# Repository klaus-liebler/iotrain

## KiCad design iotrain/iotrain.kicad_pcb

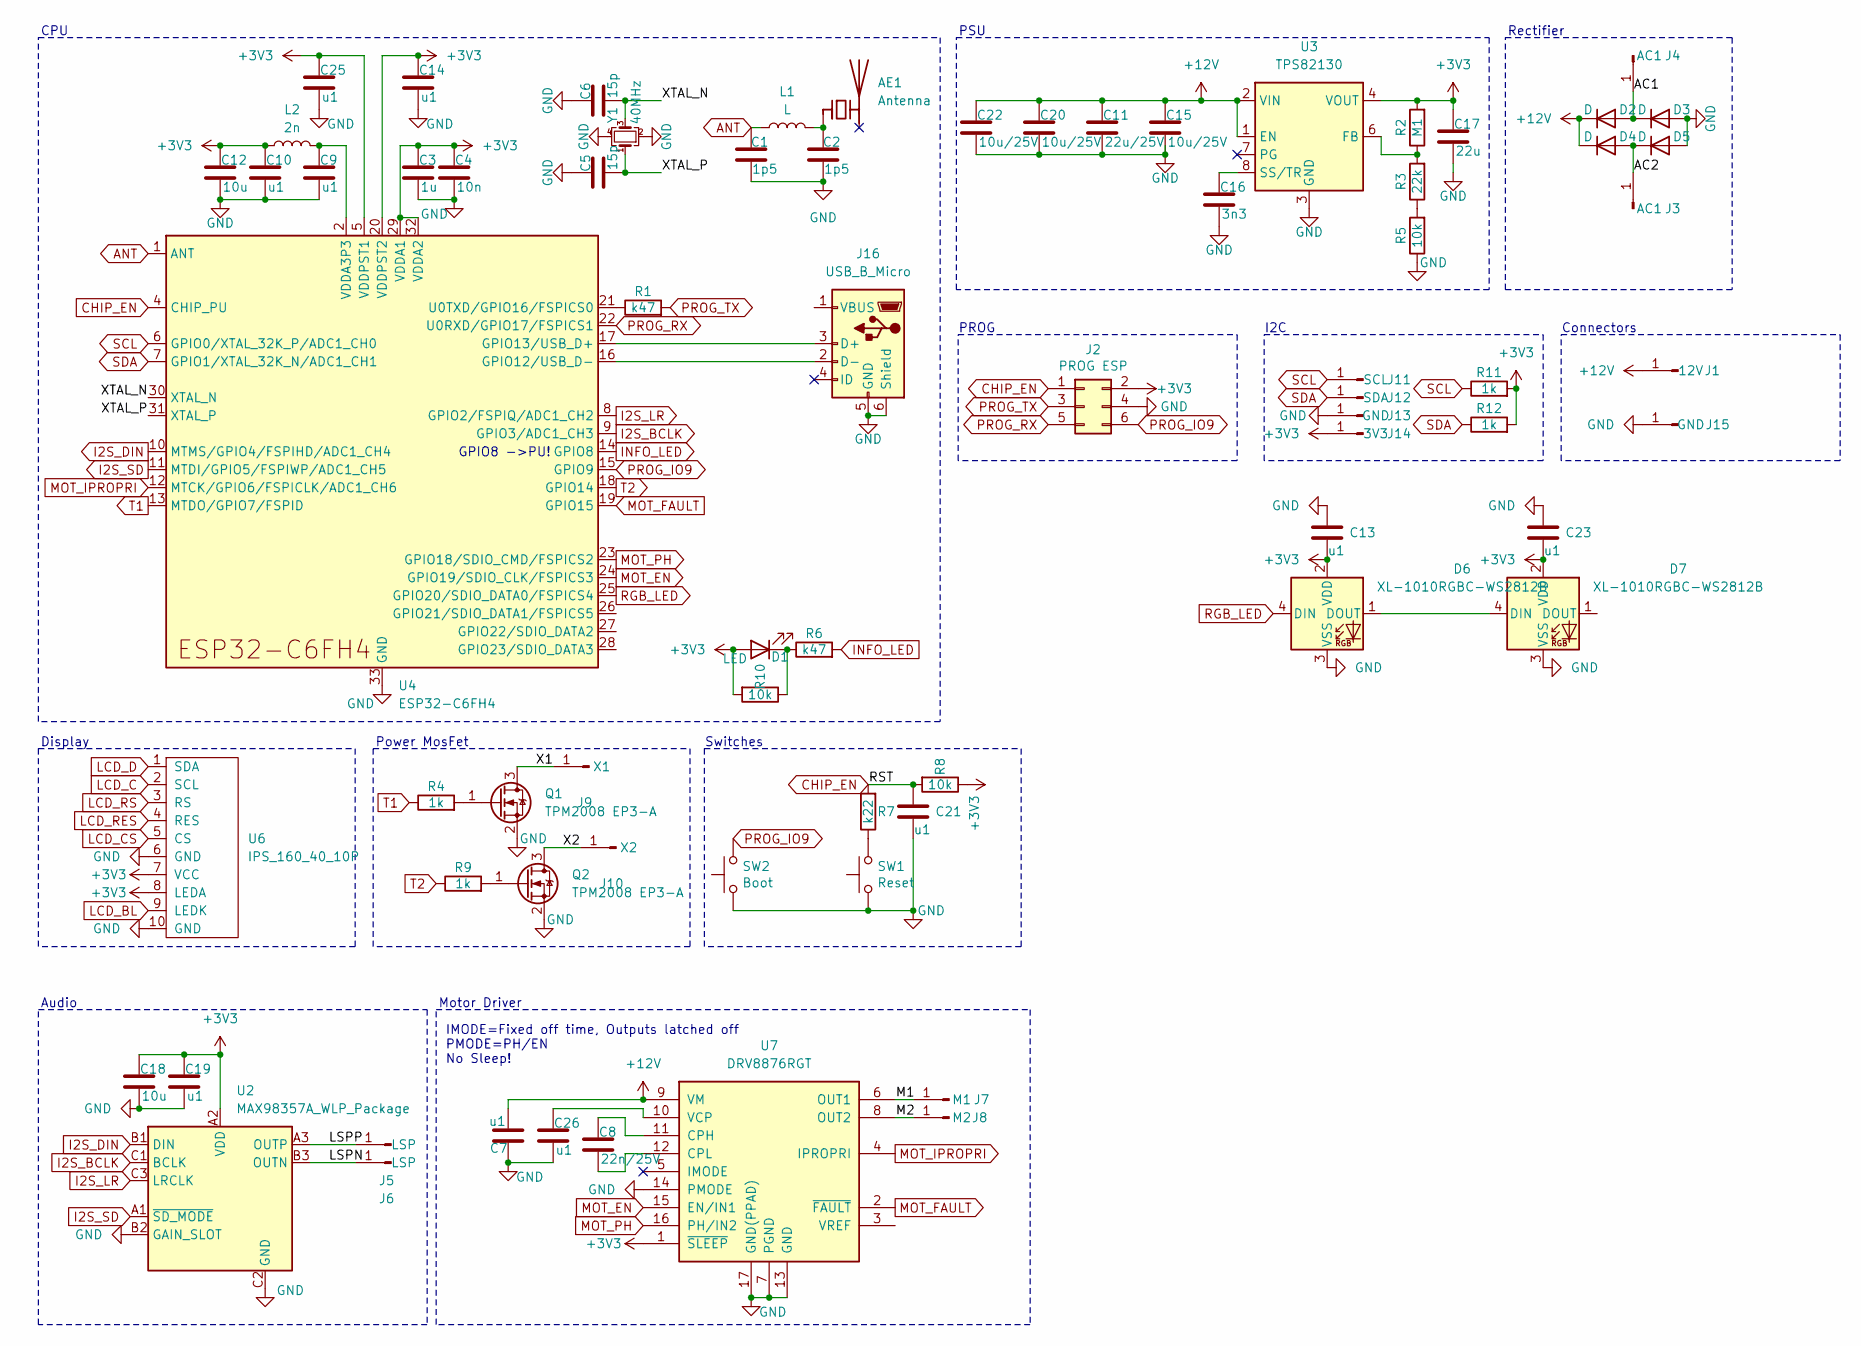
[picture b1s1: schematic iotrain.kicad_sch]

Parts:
AE1: Antenna; Johanson_2450AT18x100
C1, C2: 1p5; SMD0201
C3: 1u; SMD0201
C4: 10n; SMD0201
C5, C6: 15p; SMD0201
C7, C9, C10, C13, C14, C19, C21, C23, C25, C26: u1; SMD0201
C8: 22n/25V; SMD0201
C11: 22u/25V; SMD0805
C12, C18: 10u; SMD0402
C15, C20, C22: 10u/25V; SMD0603
C16: 3n3; SMD0201
C17: 22u; SMD0402
D1: LED; LED_0402_1005Metric
D2, D3, D4, D5: D; D_SOD-123F_smaller
D6, D7: XL-1010RGBC-WS2812B
J1: 12V; SolderWirePad_1x01_SMD_1x2mm
J2: PROG ESP; Tag-Connect_TC2030-IDC-NL_2x03_P1.27mm_Vertical
J3, J4: AC1; SolderWirePad_1x01_SMD_1x2mm
J5, J6: LSP; SolderWirePad_1x01_SMD_1x2mm
J7: M1; SolderWirePad_1x01_SMD_1x2mm
J8: M2; SolderWirePad_1x01_SMD_1x2mm
J9: X1; SolderWirePad_1x01_SMD_1x2mm
J10: X2; SolderWirePad_1x01_SMD_1x2mm
J11: SCL; SolderWirePad_1x01_SMD_1x2mm
J12: SDA; SolderWirePad_1x01_SMD_1x2mm
J13, J15: GND; SolderWirePad_1x01_SMD_1x2mm
J14: 3V3; SolderWirePad_1x01_SMD_1x2mm
J16: USB_B_Micro; USB_Micro-B_Amphenol_10104110_Horizontal
L1: L; SMD0201
L2: 2n; SMD0201
Q1, Q2: TPM2008 EP3-A; Diodes_DFN1006-3
R1, R6: k47; SMD0201
R2: M1; SMD0201
R3: 22k; SMD0201
R4, R9, R11, R12: 1k; SMD0201
R5, R8, R10: 10k; SMD0201
R7: k22; SMD0201
SW1: Reset; SW_Push_SPST_NO_Alps_SKRK
SW2: Boot; SW_Push_SPST_NO_Alps_SKRK
U2: MAX98357A_WLP_Package; WLP-9_1.448x1.468mm_Layout3x3_P0.4mm_Ball0.27mm_Pad0.25mm
U3: TPS82130; Texas_SIL0008D_MicroSiP-8-1EP_2.8x3mm_P0.65mm_EP1.1x1.9mm_T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
U4: ESP32-C6FH4; QFN-32-1EP_5x5mm_P0.5mm_EP3.6x3.6mm
U6: IPS_160_40_10P; IPS LCD 0.99 40x160
U7: DRV8876RGT; UQFN-16-1EP_3x3mm_P0.5mm_EP1.75x1.75mm
Y1: 40MHz; Crystal_SMD_2016-4Pin_2.0x1.6mm

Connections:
+3V3: C3.1, C4.1, C10.1, C12.1, C13.2, C14.1, C17.1, C18.1, C19.1, C23.2, C25.1, D1.2 (A), D6.2 (VDD), D7.2 (VDD), J2.2, J14.1, L2.1, R2.2, R8.1, R10.2, R11.2, R12.2, U2.A2 (VDD), U3.4 (VOUT), U3.5 (VOUT), U4.5 (VDDPST1), U4.20 (VDDPST2), U4.29 (VDDA1), U4.32 (VDDA2), U6.7 (VCC), U6.8 (LEDA), U7.1 (~SLEEP); also elsewhere on the board
+12V: C7.2, C11.1, C15.1, C20.1, C22.1, D2.1 (K), D4.1 (K), J1.1, U3.1 (EN), U3.2 (VIN), U7.9 (VM)
/AC1: D2.2 (A), D3.1 (K), J4.1
/AC2: D4.2 (A), D5.1 (K), J3.1
/LSPN: J6.1, U2.B3 (OUTN)
/LSPP: J5.1, U2.A3 (OUTP)
/M1: J7.1, U7.6 (OUT1)
/M2: J8.1, U7.8 (OUT2)
/X1: J9.1, Q1.3 (D)
/X2: J10.1, Q2.3 (D)
/XTAL_N: C6.2, U4.30 (XTAL_N), Y1.3
/XTAL_P: C5.2, U4.31 (XTAL_P), Y1.1
ANT: C1.1, L1.2, U4.1 (ANT)
CHIP_EN: C21.1, J2.1, R7.2, R8.2, U4.4 (CHIP_PU)
GND: C1.2, C2.2, C3.2, C4.2, C5.1, C6.1, C7.1, C9.2, C10.2, C11.2, C12.2, C13.1, C14.2, C15.2, C16.2, C17.2, C18.2, C19.2, C20.2, C21.2, C22.2, C23.1, C25.2, C26.2, D3.2 (A), D5.2 (A), D6.3 (VSS), D7.3 (VSS), J2.4, J13.1, J15.1, J16.5 (GND), J16.6 (Shield), Q1.2 (S), Q2.2 (S), R5.1, SW1.1, SW2.1, U2.B2 (GAIN_SLOT), U2.C2 (GND), U3.3 (GND), U3.9 (GND), U4.33 (GND), U6.6 (GND), U6.10 (GND), U7.7 (PGND), U7.13 (GND), U7.14 (PMODE), U7.17 (GND(PPAD)), Y1.2, Y1.4; also elsewhere on the board
I2S_BCLK: U2.C1 (BCLK), U4.9 (GPIO3/ADC1_CH3)
I2S_DIN: U2.B1 (DIN), U4.10 (MTMS/GPIO4/FSPIHD/ADC1_CH4)
I2S_LR: U2.C3 (LRCLK), U4.8 (GPIO2/FSPIQ/ADC1_CH2)
I2S_SD: U2.A1 (~SD_MODE), U4.11 (MTDI/GPIO5/FSPIWP/ADC1_CH5)
INFO_LED: R6.2, U4.14 (GPIO8)
LCD_BL: U6.9 (LEDK)
LCD_C: U6.2 (SCL)
LCD_CS: U6.5 (CS)
LCD_D: U6.1 (SDA)
LCD_RES: U6.4 (RES)
LCD_RS: U6.3 (RS)
MOT_EN: U4.24 (GPIO19/SDIO_CLK/FSPICS3), U7.15 (EN/IN1)
MOT_FAULT: U4.19 (GPIO15), U7.2 (~FAULT)
MOT_IPROPRI: U4.12 (MTCK/GPIO6/FSPICLK/ADC1_CH6), U7.4 (IPROPRI)
MOT_PH: U4.23 (GPIO18/SDIO_CMD/FSPICS2), U7.16 (PH/IN2)
unnamed: AE1.1 (FEED), C2.1, L1.1
unnamed: C9.1, L2.2, U4.2 (VDDA3P3), U4.3 (VDDA3P3)
unnamed: D1.1 (K), R6.1, R10.1
unnamed: D6.1 (DOUT), D7.4 (DIN)
unnamed: J16.3 (D+), U4.17 (GPIO13/USB_D+)
unnamed: J16.2 (D-), U4.16 (GPIO12/USB_D-)
unnamed: Q1.1 (G), R4.2
unnamed: Q2.1 (G), R9.2
unnamed: R3.1, R5.2
unnamed: R7.1, SW1.2
unnamed: R2.1, R3.2, U3.6 (FB)
unnamed: C16.1, U3.8 (SS/TR)
unnamed: R1.1, U4.21 (U0TXD/GPIO16/FSPICS0)
unnamed: C8.1, U7.11 (CPH)
unnamed: C8.2, U7.12 (CPL)
unnamed: C26.1, U7.10 (VCP)
PROG_IO9: J2.6, SW2.2, U4.15 (GPIO9)
PROG_RX: J2.5, U4.22 (U0RXD/GPIO17/FSPICS1)
PROG_TX: J2.3, R1.2
RGB_LED: D6.4 (DIN), U4.25 (GPIO20/SDIO_DATA0/FSPICS4)
SCL: J11.1, R11.1, U4.6 (GPIO0/XTAL_32K_P/ADC1_CH0)
SDA: J12.1, R12.1, U4.7 (GPIO1/XTAL_32K_N/ADC1_CH1)
T1: R4.1, U4.13 (MTDO/GPIO7/FSPID)
T2: R9.1, U4.18 (GPIO14)

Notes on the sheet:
IMODE=Fixed off time, Outputs latched off PMODE=PH/EN No Sleep!
I2C
Rectifier
Connectors
PSU
CPU
Switches
Display
Audio
GPIO8 ->PU!
Power MosFet
Motor Driver
PROG

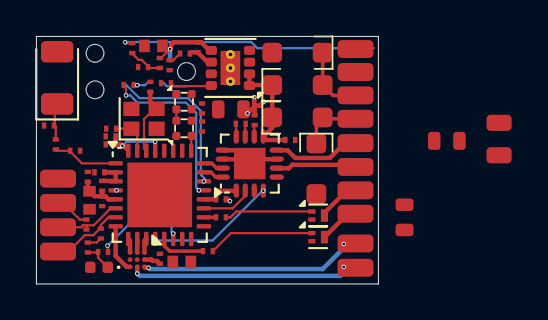
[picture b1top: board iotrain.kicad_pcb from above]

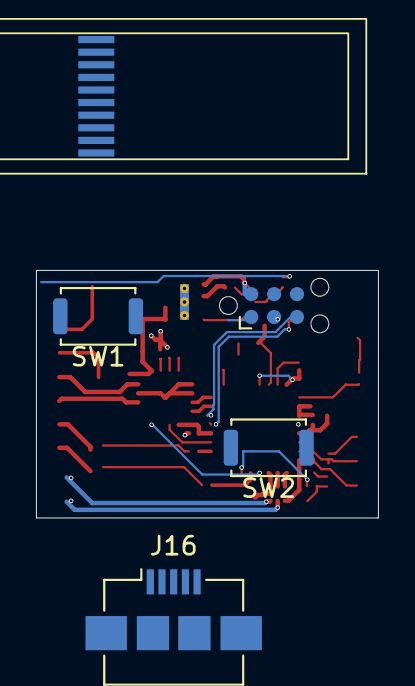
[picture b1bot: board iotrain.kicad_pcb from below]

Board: 2 copper layers, 19.0 x 13.8 mm, 73 parts (5 on the bottom side), 48 nets.

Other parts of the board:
C3#2: 1u; SMD0201
C4#2: 10n; SMD0201

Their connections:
+3V3: C3#2.1, C4#2.1; also elsewhere on the board
GND: C3#2.2, C4#2.2; also elsewhere on the board

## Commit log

2024-10-02 ESP32-C6
2024-10-03 Slightly improved placement -->22x14mm
2024-10-06 Make it smaller
2024-10-07 Beautified
2024-10-07 various
2025-03-10 Deleted backups
